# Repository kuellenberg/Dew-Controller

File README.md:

# Dew Controller

Microcontroller based project to control dew heater straps used on a telescope.

## Specification
* Operating voltage: 12V dc
* Power consumption (idle): t.b.d.
* 4 independently controlled heater channels
  * RCA jacks
  * Electronic overcurrent and short circuit protection
  * Total output current: 3.5 A max.
* 12 x 2 OLED display
* External temperature and humidity sensor connected via RS232 interface
  * Uses Silicon Labs Si7006 precision sensor
    * +/-1°C max.
    * +/-5% RH max.
* Auxiliary NTC temperature sensor input for testing and calibration
* User-friendly menu with rotary encoder input

## Theory of operation
The dew controller continuously calculates the required heating power for each connected dew heater strap based upon lens diameter and current temperature and humidity conditions. By carefully controlling the heating power negative seeing effects caused by undesired air movements are reduced to a minimum.
The underlying algorithm compensates for the rate of heat flow from the telescope lens to the cold sky, assuming that the telescope is equipped with a dew shield and only the circular area of the lens is exposed to the sky. An adjustable 'fudge factor' copes with all other deficiencies, like lack of thermal insulation from the heater straps. The theory gives very simular results to the rule of thumb given by [1].

## Hardware
### Controller Unit

The dew controller is build around a PIC16F15356 microcontroller with 16k words of flash memory and 2kB of RAM. It is configured to run at a clock frequency of 4.0 MHz, generated by its internal oscillator. With hindsight, regarding flash memory size and the string constants required by the menu system, the part wasn't the optimal choice. Without compiler optimizations the code doesn't fit on the device. For the next revision of the hardware a pin compatible PIC18F should be considered.

Since the controller has to be capable of measuring the current on each heater channel, the circuit comprises a TI INA180 high side current sense amplifier. To reduce cost and complexity, only a single amplifier is used and firmware measures the current of each channel sequentially. As for overcurrent and short circuit protection, an integrated solution is used. The Vishay SiP32419 is a load switch with programmable current limit up to 3.5A and eliminates the need for a conventional fuse (for which you'll never bring any spares, when you operate the device on a field trip).

The input voltage is measured with a simple voltage divider, buffered by 1/2 LM358. The other half of the Opamp is used for buffering the auxiliary NTC temperature sensor input.

It turned out that the switch mode regulator used on the OLED display module injects a lot of conducted noise back into the supply rails, which seriously impacts the performance of the microcontroller's ADC. The easiest way to block the noise from getting into the microcontroller was using a dedicated linear regulator for the display module. The regulator can be turned off via a MOSFET to save power during standby operation.

The device's menu system is entirely operated by a single rotary encoder with integrated push button. Although the quadrature signals are rudimentary low pass filtered, further debouncing is required in software.

High side P-channel MOSFETs are used to operate the four heater channels. 

The external temperature and humidity sensor is connected via an RS-232 interface, providing flexibility when testing different types of sensors. Although technically, the RS-232 level shifter isn't necessary if short cables are used, it gives good ESD protection and some extra noise immunity.

#### Case design
The housing is designed with [Schaeffer AG Frontplatten Designer](https://www.schaeffer-ag.de/frontplatten-designer)

### Sensor Box
The sensor circuit is very simple. It uses the PIC16F325 with 8k words flash memory and 1kB RAM. Unlike the controller circuit, it is powered by a 3.3V regulator. The Si7006 temperature and humidity sensor via connected I2C. RS-232 level shifting is done by a MAX3232. The PCB is designed to fit into a Hammond 1551 case with custom lid.

## Firmware
Firmware development is done in MPLAB X with XC8 compiler. 

t.b.c.

___
[1]: G. D. Roth, Handbuch für Sternfreunde. Band 1: Technik und Theorie. ISBN 978-3-662-35367-7

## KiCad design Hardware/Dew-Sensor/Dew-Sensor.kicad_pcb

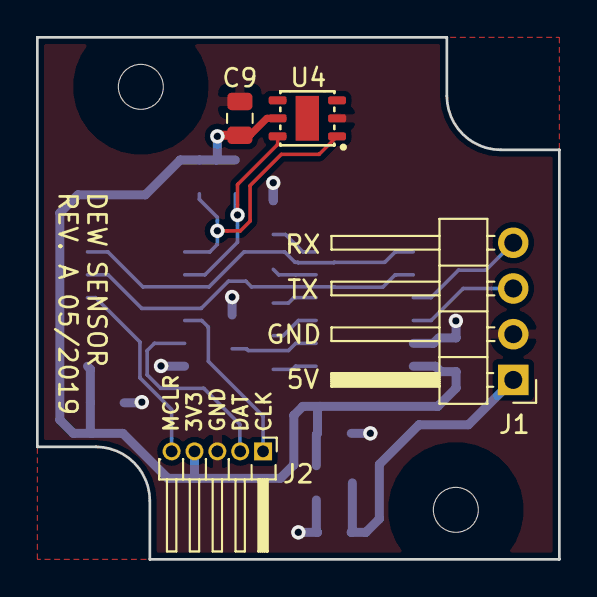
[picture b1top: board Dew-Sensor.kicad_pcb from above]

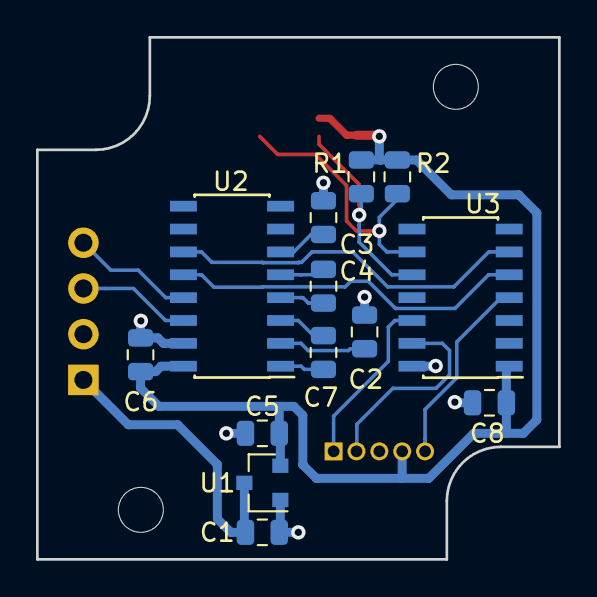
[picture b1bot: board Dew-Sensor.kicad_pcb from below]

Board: 2 copper layers, 29.0 x 29.0 mm, 19 parts (13 on the bottom side), 18 nets.

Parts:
C1, C2, C3, C4, C5, C6, C7, C8, C9: 100nF; C_0805_2012Metric
H1, H2: MountingHole; MountingHole_2.5mm
J1: Conn_01x04; PinHeader_1x04_P2.54mm_Horizontal
J2: Conn_01x05; PinHeader_1x05_P1.27mm_Horizontal
R1, R2: 10k; R_0805_2012Metric
U1: MCP1703A-3302_SOT23; SOT-23
U2: MAX3232; SOIC-16_3.9x9.9mm_P1.27mm
U3: PIC16(L)F15323_14DIP_SOIC_TSSOP; SOIC-14_3.9x8.7mm_P1.27mm
U4: Si7006; SI7006-A20

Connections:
+3V3: C5.1, C6.1, C8.1, C9.1, J2.4, R1.1, R2.1, U1.2, U2.16, U3.1, U4.5
+5V: C1.1, J1.1, U1.3
/ICSPCLK: J2.1, U3.12
/ICSPDAT: J2.2, U3.13
/MCLR: J2.5, U3.4
/RX: U2.12, U3.5
/RX-IN: J1.4, U2.13
/SCL: R1.2, U3.10, U4.6
/SDA: R2.2, U3.9, U4.1
/TX: U2.11, U3.6
/TX-OUT: J1.3, U2.14
GND: C1.2, C2.2, C3.1, C5.2, C6.2, C8.2, C9.2, J1.2, J2.3, U1.1, U2.15, U3.14, U4.2
unnamed: C2.1, U2.2
unnamed: C3.2, U2.6
unnamed: C4.1, U2.4
unnamed: C4.2, U2.5
unnamed: C7.1, U2.1
unnamed: C7.2, U2.3

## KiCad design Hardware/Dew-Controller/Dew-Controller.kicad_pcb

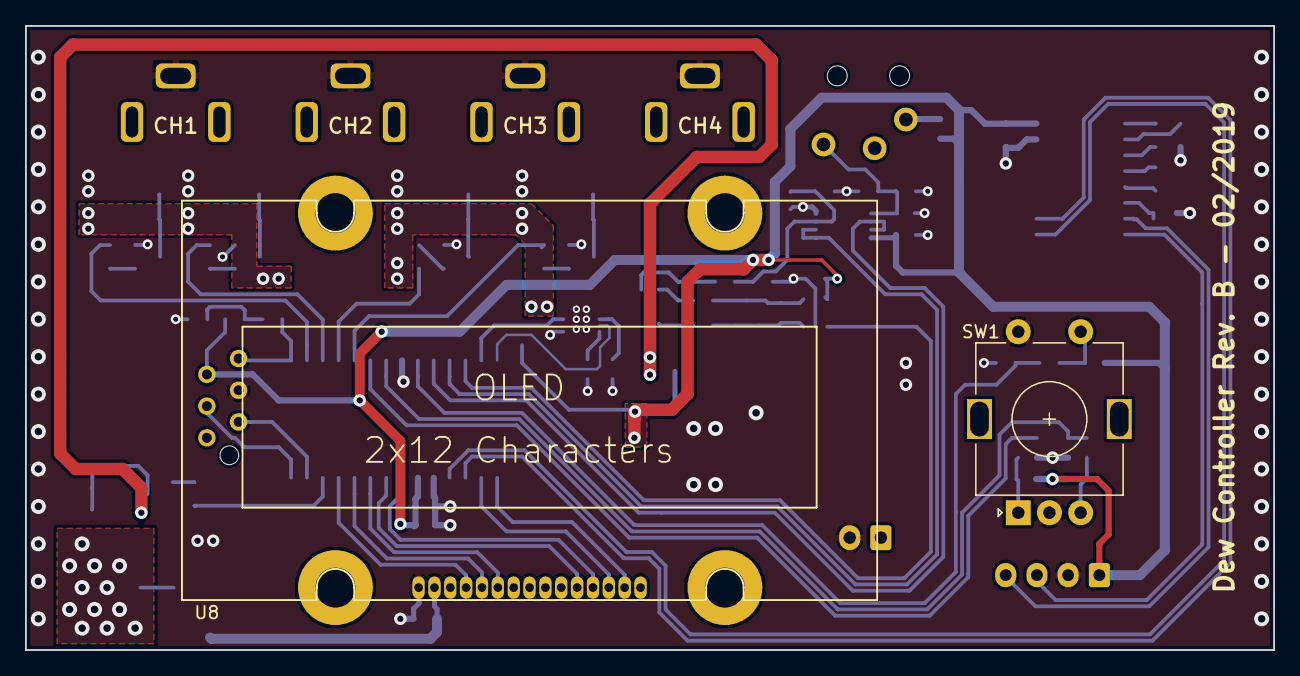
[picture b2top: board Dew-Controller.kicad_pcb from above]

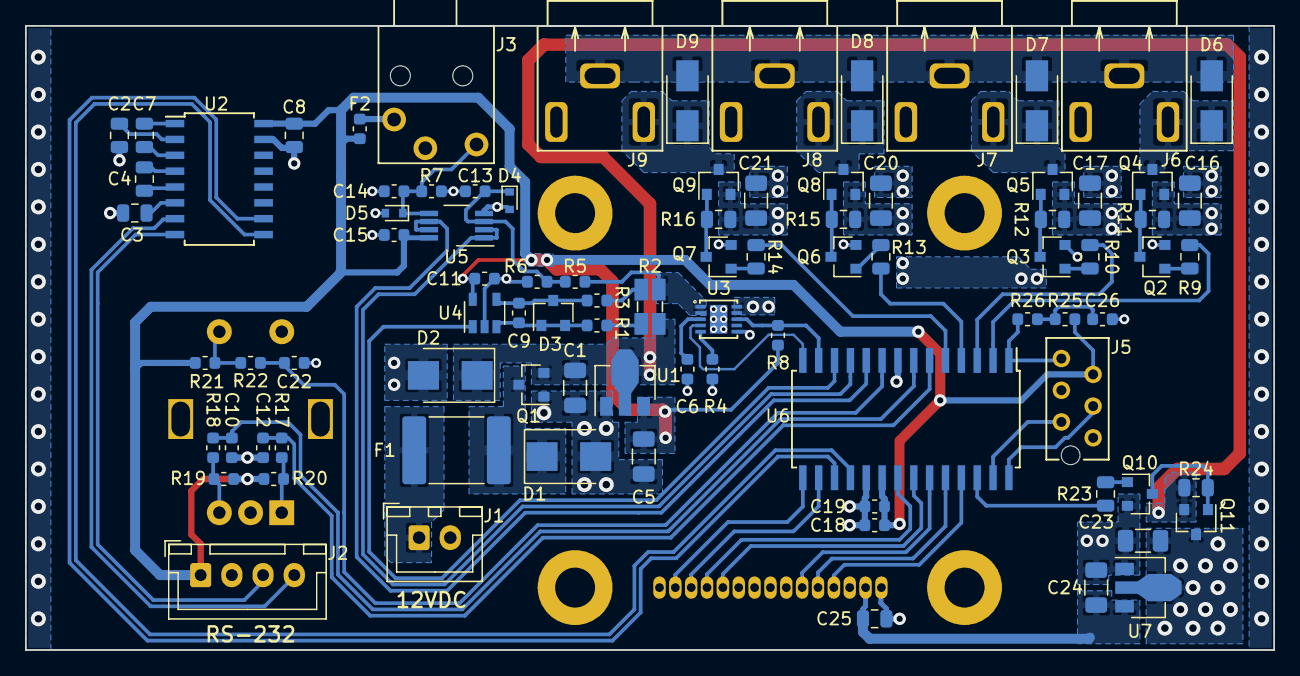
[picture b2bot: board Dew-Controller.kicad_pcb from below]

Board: 2 copper layers, 100.0 x 50.0 mm, 92 parts (89 on the bottom side), 69 nets.

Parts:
C1, C5, C16, C17, C20, C21, C23, C24: 10uF; C_1206_3216Metric
C2, C3, C4, C7, C8: 1uF; C_0805_2012Metric
C6, C9, C10, C12, C22, C26: 10nF; C_0603_1608Metric
C11, C13, C14, C15, C19: 100nF; C_0603_1608Metric
C18: 1uF; C_0603_1608Metric
C25: 100nF; C_0805_2012Metric
D1: 15V; D_SMB
D2: 15V, 3W; D_SMB
D3: BAT54S; SOT-23
D4, D5: 5V6; D_SOD-523
D6, D7, D8, D9: SMAJ12A; D_SMA
F1: 3A; Fuse_2920_7451Metric
F2: 50mA; Fuse_0603_1608Metric
G1: Lemonhead; lemonhead
J1: POWER; JST_XH_B02B-XH-A_1x02_P2.50mm_Vertical
J2: RS232; JST_XH_B04B-XH-A_1x04_P2.50mm_Vertical
J3: Temp; MJ-2509N
J5: ICSP; MicroMatch-Female-6P
J6: CH1; PJRAN1X1U
J7: CH2; PJRAN1X1U
J8: CH3; PJRAN1X1U
J9: CH4; PJRAN1X1U
Q1, Q4, Q5, Q8, Q9, Q11: SI2369DS; SOT-23
Q2, Q3, Q6, Q7, Q10: BSS138; SOT-23
R1, R3: 4R7; R_0603_1608Metric
R2: 0R05; R_Shunt_Ohmite_LVK12
R4: 2k8; R_0603_1608Metric
R5: 150k; R_0603_1608Metric
R6: 47k; R_0603_1608Metric
R7, R17, R18, R19, R20, R21, R22, R25: 10k; R_0603_1608Metric
R8: 100k; R_0603_1608Metric
R9, R10, R13, R14, R23: 100R; R_0805_2012Metric
R11, R12, R15, R16, R24: 10k; R_0805_2012Metric
R26: 470R; R_0603_1608Metric
SW1: Rotary_Encoder_Switch; RotaryEncoder_Alps_EC11E-Switch_Vertical_H20mm
U1, U7: MCP1703A-5002_SOT89; SOT-89-3
U2: MAX232; SOIC-16W_5.3x10.2mm_P1.27mm
U3: SIP32419; DFN-10-1EP_3x3mm_P0.5mm_EP1.4x2.3mm
U4: INA180-A2; SOT-23-5
U5: LM358; VSSOP-8_3.0x3.0mm_P0.65mm
U6: PIC16(L)F15354_28DIP_SOIC_SSOP; SOIC-28W_7.5x17.9mm_P1.27mm
U8: OLED-012N002A; OLED012N002A

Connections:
+5V: C5.1, C8.1, C11.1, C15.1, C18.1, C19.1, F2.1, J2.1, J5.2, R8.1, R19.1, R20.1, R21.1, R25.1, U1.3, U2.16, U4.5, U5.8, U6.20
+5VP: C24.1, C25.1, U7.3, U8.2
+12P: C23.1, Q11.3, U7.2
+12V: C1.1, D2.1, Q1.2, Q11.2, R2.1, R24.1, U1.2
+VSW: C16.1, C17.1, C20.1, C21.1, Q4.2, Q5.2, Q8.2, Q9.2, R11.2, R12.2, R15.2, R16.2, U3.9, U3.10
/DB0: U6.22, U8.11
/DB1: U6.21, U8.12
/DB2: U6.16, U8.13
/DB3: U6.15, U8.14
/EN: U6.23, U8.6
/ICSPCLK: J5.5, U6.27
/ICSPDAT: J5.4, U6.28
/ISENS: U4.1, U6.12
/MCLR: J5.1, R26.1, U6.1
/OLED_PWR: R23.2, U6.26
/PEN: U3.4, U6.14
/ROT_A: C12.1, R17.2, U6.6
/ROT_B: C10.1, R18.2, U6.7
/ROT_PB: C22.1, R22.1, U6.9
/RS: U6.25, U8.4
/RW: U6.24, U8.5
/RX: U2.9, U6.18
/RX-IN: J2.3, U2.8
/SW_CH1: R9.2, U6.2
/SW_CH2: R10.2, U6.3
/SW_CH3: R13.2, U6.4
/SW_CH4: R14.2, U6.5
/TEMP: U5.6, U5.7, U6.10
/TX: U2.10, U6.17
/TX-OUT: J2.4, U2.7
/VSENS: U5.1, U5.2, U6.11
/~FAULT: R8.2, U3.8, U6.13
GND: C1.2, C2.2, C3.1, C5.2, C6.2, C8.2, C10.2, C11.2, C12.2, C13.2, C14.2, C15.2, C16.2, C17.2, C18.2, C19.2, C20.2, C21.2, C22.2, C23.2, C24.2, C25.2, C26.2, D1.2, D2.2, D4.2, D5.2, D6.2, D7.2, D8.2, D9.2, J1.2, J2.2, J5.3, J6.2, J7.2, J8.2, J9.2, Q1.1, Q2.2, Q3.2, Q6.2, Q7.2, Q10.2, R4.2, R6.2, R7.2, SW1.C, SW1.S2, U1.1, U2.15, U3.6, U3.11, U4.2, U5.4, U6.8, U6.19, U7.1, U8.1
unnamed: C2.1, U2.2
unnamed: C3.2, U2.6
unnamed: C4.1, U2.4
unnamed: C4.2, U2.5
unnamed: C6.1, U3.3
unnamed: C7.1, U2.1
unnamed: C7.2, U2.3
unnamed: C9.1, D3.1, D3.2, R1.2, U4.3
unnamed: C9.2, D3.3, R3.2, U4.4
unnamed: C13.1, D4.1, R5.2, R6.1, U5.3
unnamed: C14.1, D5.1, J3.T, R7.1, U5.5
unnamed: C26.1, R25.2, R26.2
unnamed: D1.1, F1.2, Q1.3
unnamed: D6.1, J6.1, Q4.3
unnamed: D7.1, J7.1, Q5.3
unnamed: D8.1, J8.1, Q8.3
unnamed: D9.1, J9.1, Q9.3
unnamed: F1.1, J1.1
unnamed: F2.2, J3.S
unnamed: Q2.1, R9.1
unnamed: Q2.3, Q4.1, R11.1
unnamed: Q3.1, R10.1
unnamed: Q3.3, Q5.1, R12.1
unnamed: Q6.1, R13.1
unnamed: Q6.3, Q8.1, R15.1
unnamed: Q7.1, R14.1
unnamed: Q7.3, Q9.1, R16.1
unnamed: Q10.1, R23.1
unnamed: Q10.3, Q11.1, R24.2
unnamed: R1.1, R2.2
unnamed: R2.3, R3.1
unnamed: R2.4, R5.1, U3.1, U3.2
unnamed: R4.1, U3.5
unnamed: R17.1, R20.2, SW1.A
unnamed: R18.1, R19.2, SW1.B
unnamed: R21.2, R22.2, SW1.S1

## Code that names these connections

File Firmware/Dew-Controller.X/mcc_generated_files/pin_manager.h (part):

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// get/set SW_CH1 aliases
#define SW_CH1_TRIS                 TRISAbits.TRISA0
#define SW_CH1_LAT                  LATAbits.LATA0
#define SW_CH1_PORT                 PORTAbits.RA0
#define SW_CH1_WPU                  WPUAbits.WPUA0
#define SW_CH1_OD                   ODCONAbits.ODCA0
#define SW_CH1_ANS                  ANSELAbits.ANSA0
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// get/set SW_CH2 aliases
#define SW_CH2_TRIS                 TRISAbits.TRISA1
#define SW_CH2_LAT                  LATAbits.LATA1
#define SW_CH2_PORT                 PORTAbits.RA1
#define SW_CH2_WPU                  WPUAbits.WPUA1
#define SW_CH2_OD                   ODCONAbits.ODCA1
#define SW_CH2_ANS                  ANSELAbits.ANSA1
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// get/set SW_CH3 aliases
#define SW_CH3_TRIS                 TRISAbits.TRISA2
#define SW_CH3_LAT                  LATAbits.LATA2
#define SW_CH3_PORT                 PORTAbits.RA2
#define SW_CH3_WPU                  WPUAbits.WPUA2
#define SW_CH3_OD                   ODCONAbits.ODCA2
#define SW_CH3_ANS                  ANSELAbits.ANSA2
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// get/set SW_CH4 aliases
#define SW_CH4_TRIS                 TRISAbits.TRISA3
#define SW_CH4_LAT                  LATAbits.LATA3
#define SW_CH4_PORT                 PORTAbits.RA3
#define SW_CH4_WPU                  WPUAbits.WPUA3
#define SW_CH4_OD                   ODCONAbits.ODCA3
#define SW_CH4_ANS                  ANSELAbits.ANSA3
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// get/set ROT_A aliases
#define ROT_A_TRIS                 TRISAbits.TRISA4
#define ROT_A_LAT                  LATAbits.LATA4
#define ROT_A_PORT                 PORTAbits.RA4
#define ROT_A_WPU                  WPUAbits.WPUA4
#define ROT_A_OD                   ODCONAbits.ODCA4
#define ROT_A_ANS                  ANSELAbits.ANSA4
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// get/set ROT_B aliases
#define ROT_B_TRIS                 TRISAbits.TRISA5
#define ROT_B_LAT                  LATAbits.LATA5
#define ROT_B_PORT                 PORTAbits.RA5
#define ROT_B_WPU                  WPUAbits.WPUA5
#define ROT_B_OD                   ODCONAbits.ODCA5
#define ROT_B_ANS                  ANSELAbits.ANSA5
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// get/set ROT_PB aliases
#define ROT_PB_TRIS                 TRISAbits.TRISA7
#define ROT_PB_LAT                  LATAbits.LATA7
#define ROT_PB_PORT                 PORTAbits.RA7
#define ROT_PB_WPU                  WPUAbits.WPUA7
#define ROT_PB_OD                   ODCONAbits.ODCA7
#define ROT_PB_ANS                  ANSELAbits.ANSA7
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// get/set OLED_PWR aliases
#define OLED_PWR_TRIS                 TRISBbits.TRISB5
#define OLED_PWR_LAT                  LATBbits.LATB5
#define OLED_PWR_PORT                 PORTBbits.RB5
#define OLED_PWR_WPU                  WPUBbits.WPUB5
#define OLED_PWR_OD                   ODCONBbits.ODCB5
#define OLED_PWR_ANS                  ANSELBbits.ANSB5
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// get/set VSENS aliases
#define VSENS_TRIS                 TRISCbits.TRISC0
#define VSENS_LAT                  LATCbits.LATC0
#define VSENS_PORT                 PORTCbits.RC0
#define VSENS_WPU                  WPUCbits.WPUC0
#define VSENS_OD                   ODCONCbits.ODCC0
#define VSENS_ANS                  ANSELCbits.ANSC0
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// get/set ISENS aliases
#define ISENS_TRIS                 TRISCbits.TRISC1
#define ISENS_LAT                  LATCbits.LATC1
#define ISENS_PORT                 PORTCbits.RC1
#define ISENS_WPU                  WPUCbits.WPUC1
#define ISENS_OD                   ODCONCbits.ODCC1
#define ISENS_ANS                  ANSELCbits.ANSC1
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
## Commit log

2019-08-02 Merged repos
2019-08-02 Added Case Design Files (Schaeffer AG)
2019-12-30 stuff...
2020-01-13 notes...
2020-01-14 Rewriting firmware from scratch
2020-01-14 firmware stuff
2020-01-15 stuff..
2020-01-18 added I2C code for dew sensor
2020-01-18 Finished I2C code. Dew Sensor sends data packets.
2020-01-19 Firmware stuff...
2020-01-20 Firmware...
2020-01-20 Time functions
2020-01-21 Split main.c into modules.
2020-01-25 testing
2020-01-26 Firmware
2020-01-26 Firmware...untested
2020-01-27 Firmware sprintf bug?
2020-01-28 Replaced all sprintf() with ftoa(). Testing Pset/Pmax/Preq...
2020-01-28 samples = 0
2020-01-29 Sleep-deprived coding goodness [untested]
2020-01-29 Push button now checked on 10ms timer isr after first push.
2020-01-30 Added error handling and the channelThing(tm)
2020-01-31 Added control loop [untested]
2020-01-31 Working!
2020-02-01 Clean up: Removed pointer to data. Removed single line functions.
2020-02-01 Storing configuration in flash memory.
2020-02-01 Bug fixes
2020-02-02 More bug fixes...
2020-02-02 Update sensor firmware. Clearing status bit when sensor data is implausible.
2020-02-02 Added new picture.
2020-02-03 Tests
2020-02-03 strnycpy bug fixed and fortuitous compiler farts galore...
2020-02-04 Compiles with -O1 again.
2020-02-04 Added debug mode. Needs -O3 to run.
2020-02-13 Updated schematics
2020-02-16 Readme.md

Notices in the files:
Firmware/Dew-Controller.X/mcc_generated_files/pin_manager.h:
(c) 2018 Microchip Technology Inc. and its subsidiaries.
